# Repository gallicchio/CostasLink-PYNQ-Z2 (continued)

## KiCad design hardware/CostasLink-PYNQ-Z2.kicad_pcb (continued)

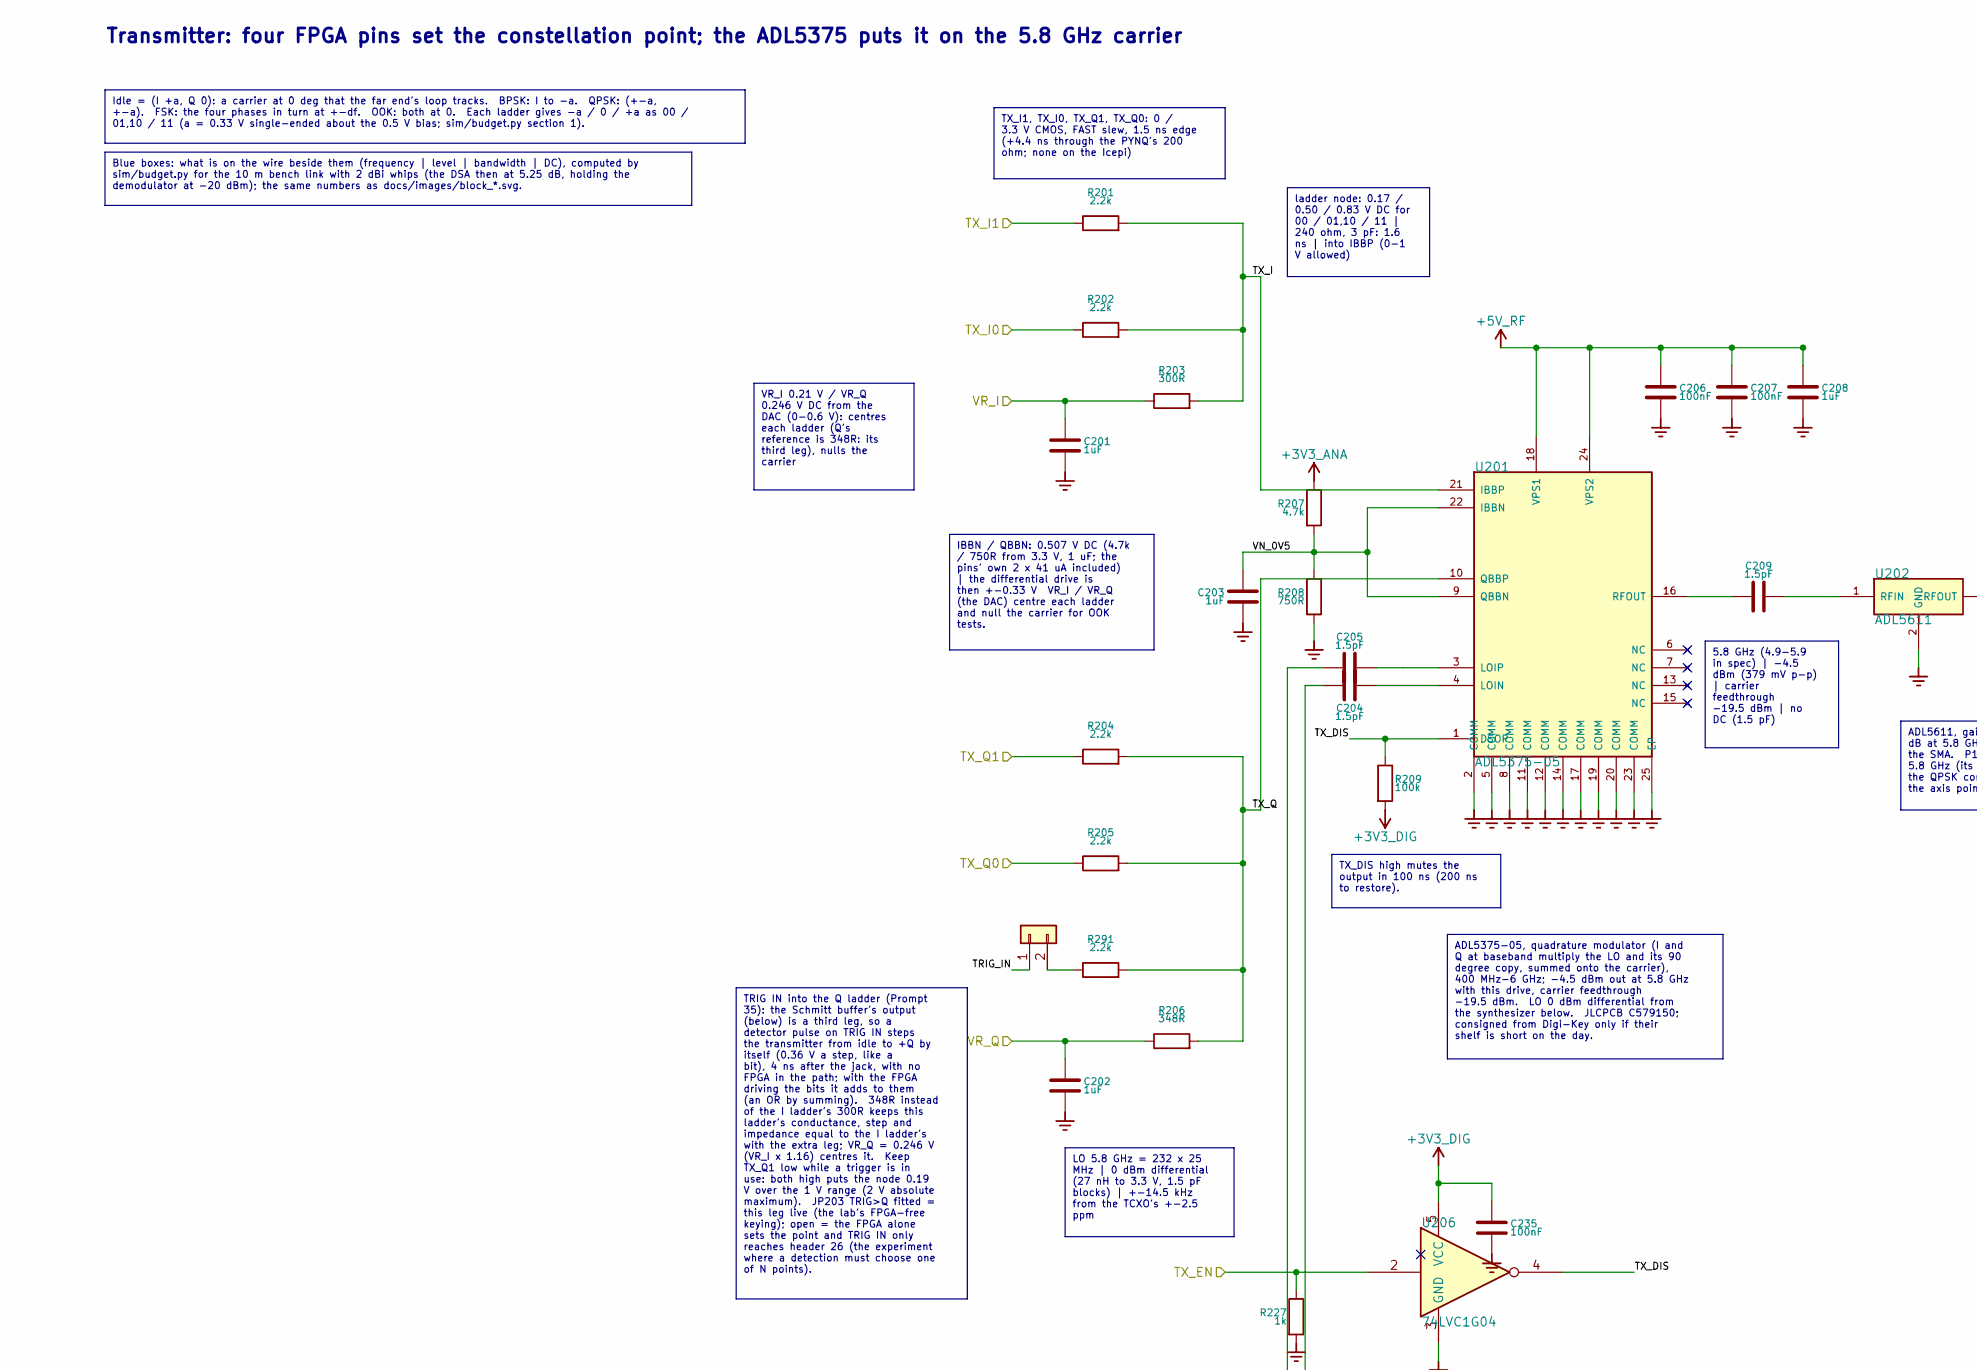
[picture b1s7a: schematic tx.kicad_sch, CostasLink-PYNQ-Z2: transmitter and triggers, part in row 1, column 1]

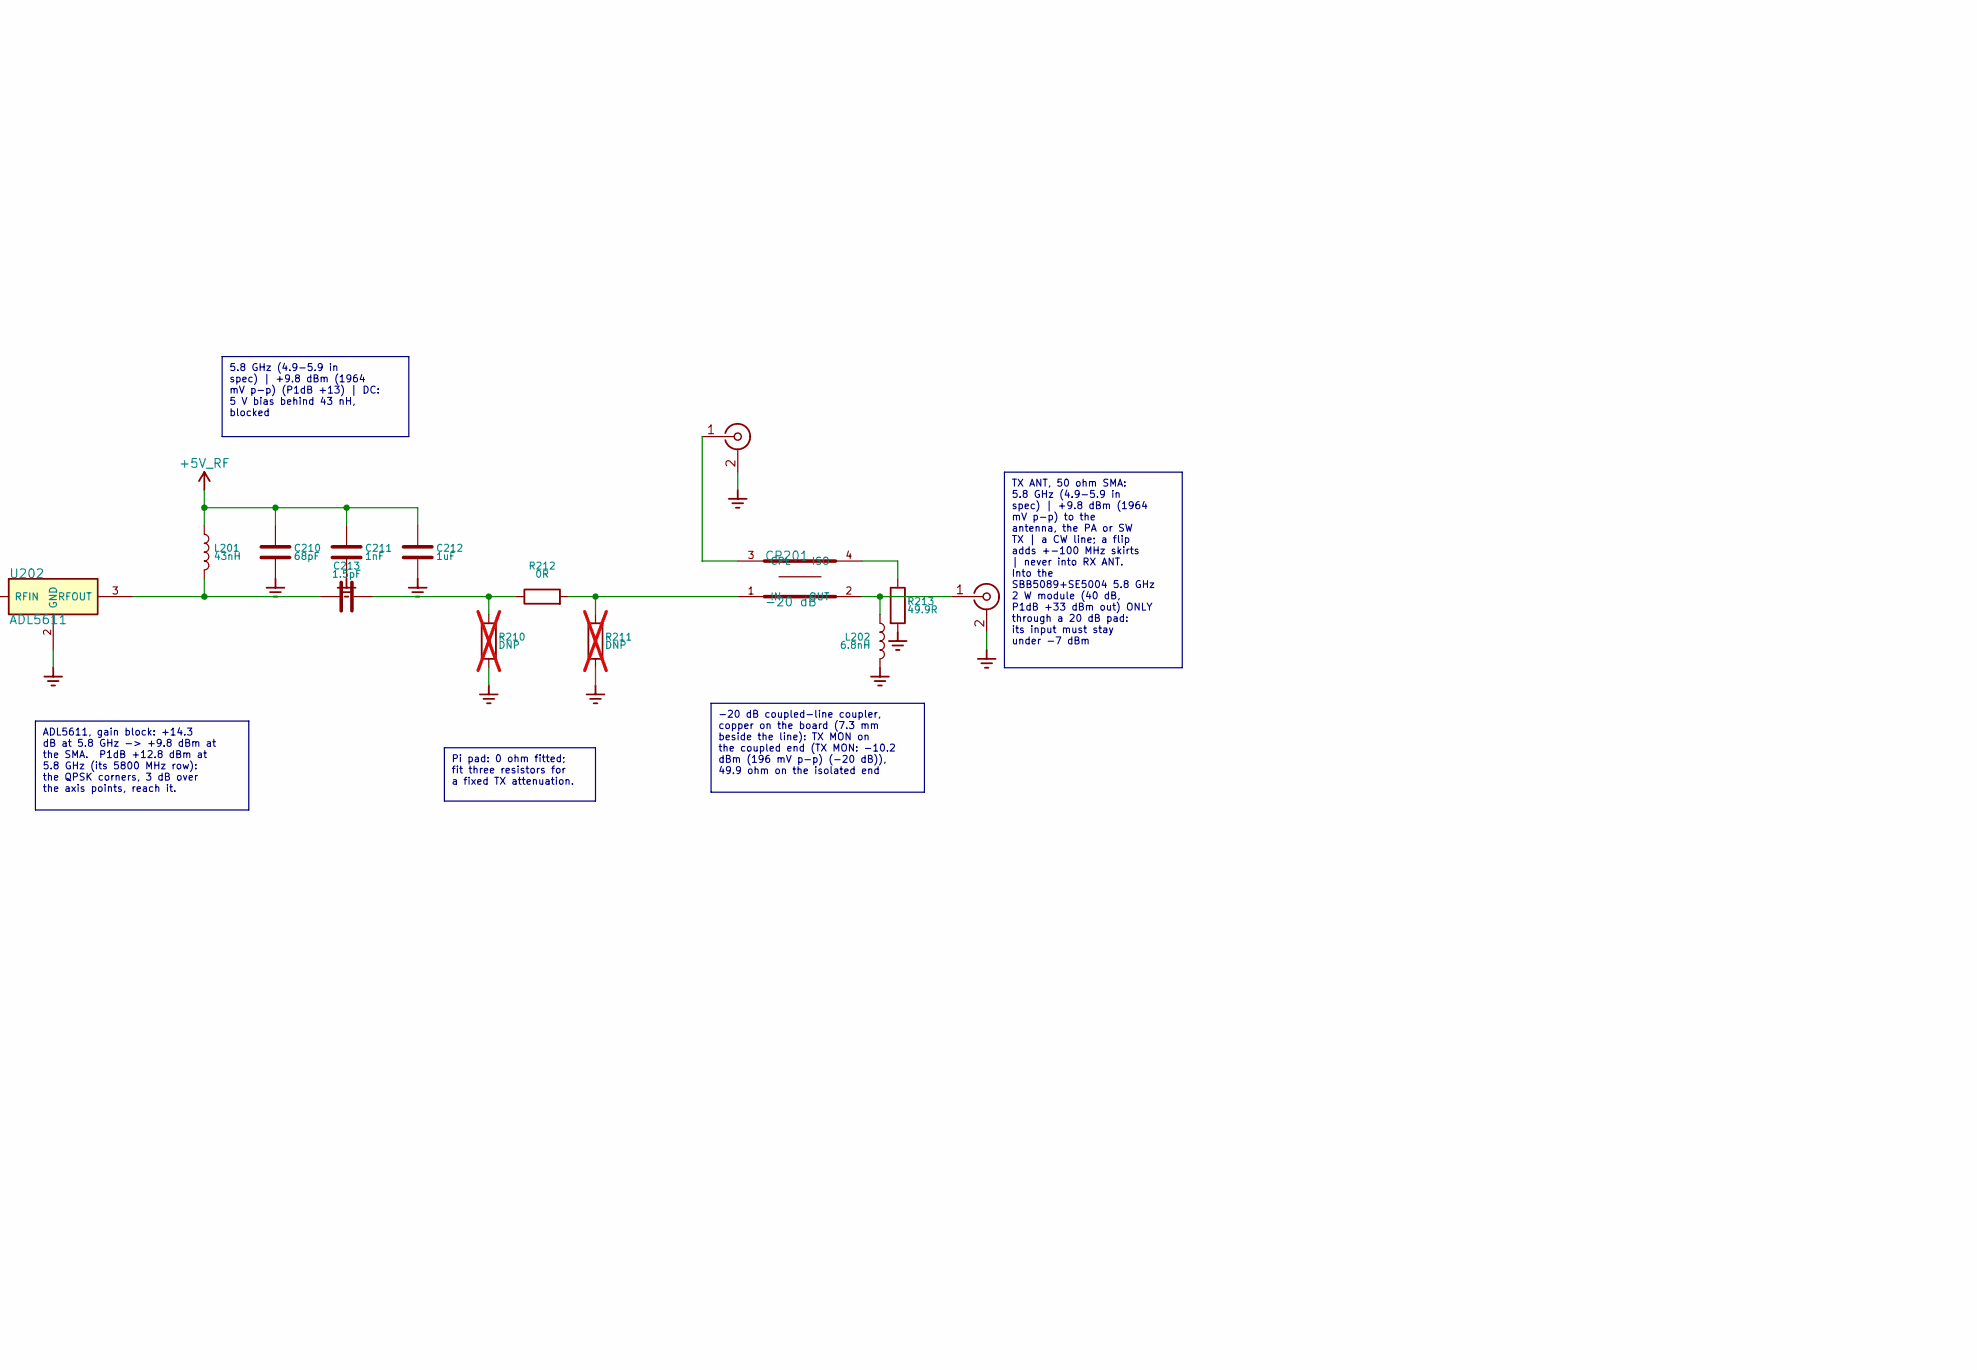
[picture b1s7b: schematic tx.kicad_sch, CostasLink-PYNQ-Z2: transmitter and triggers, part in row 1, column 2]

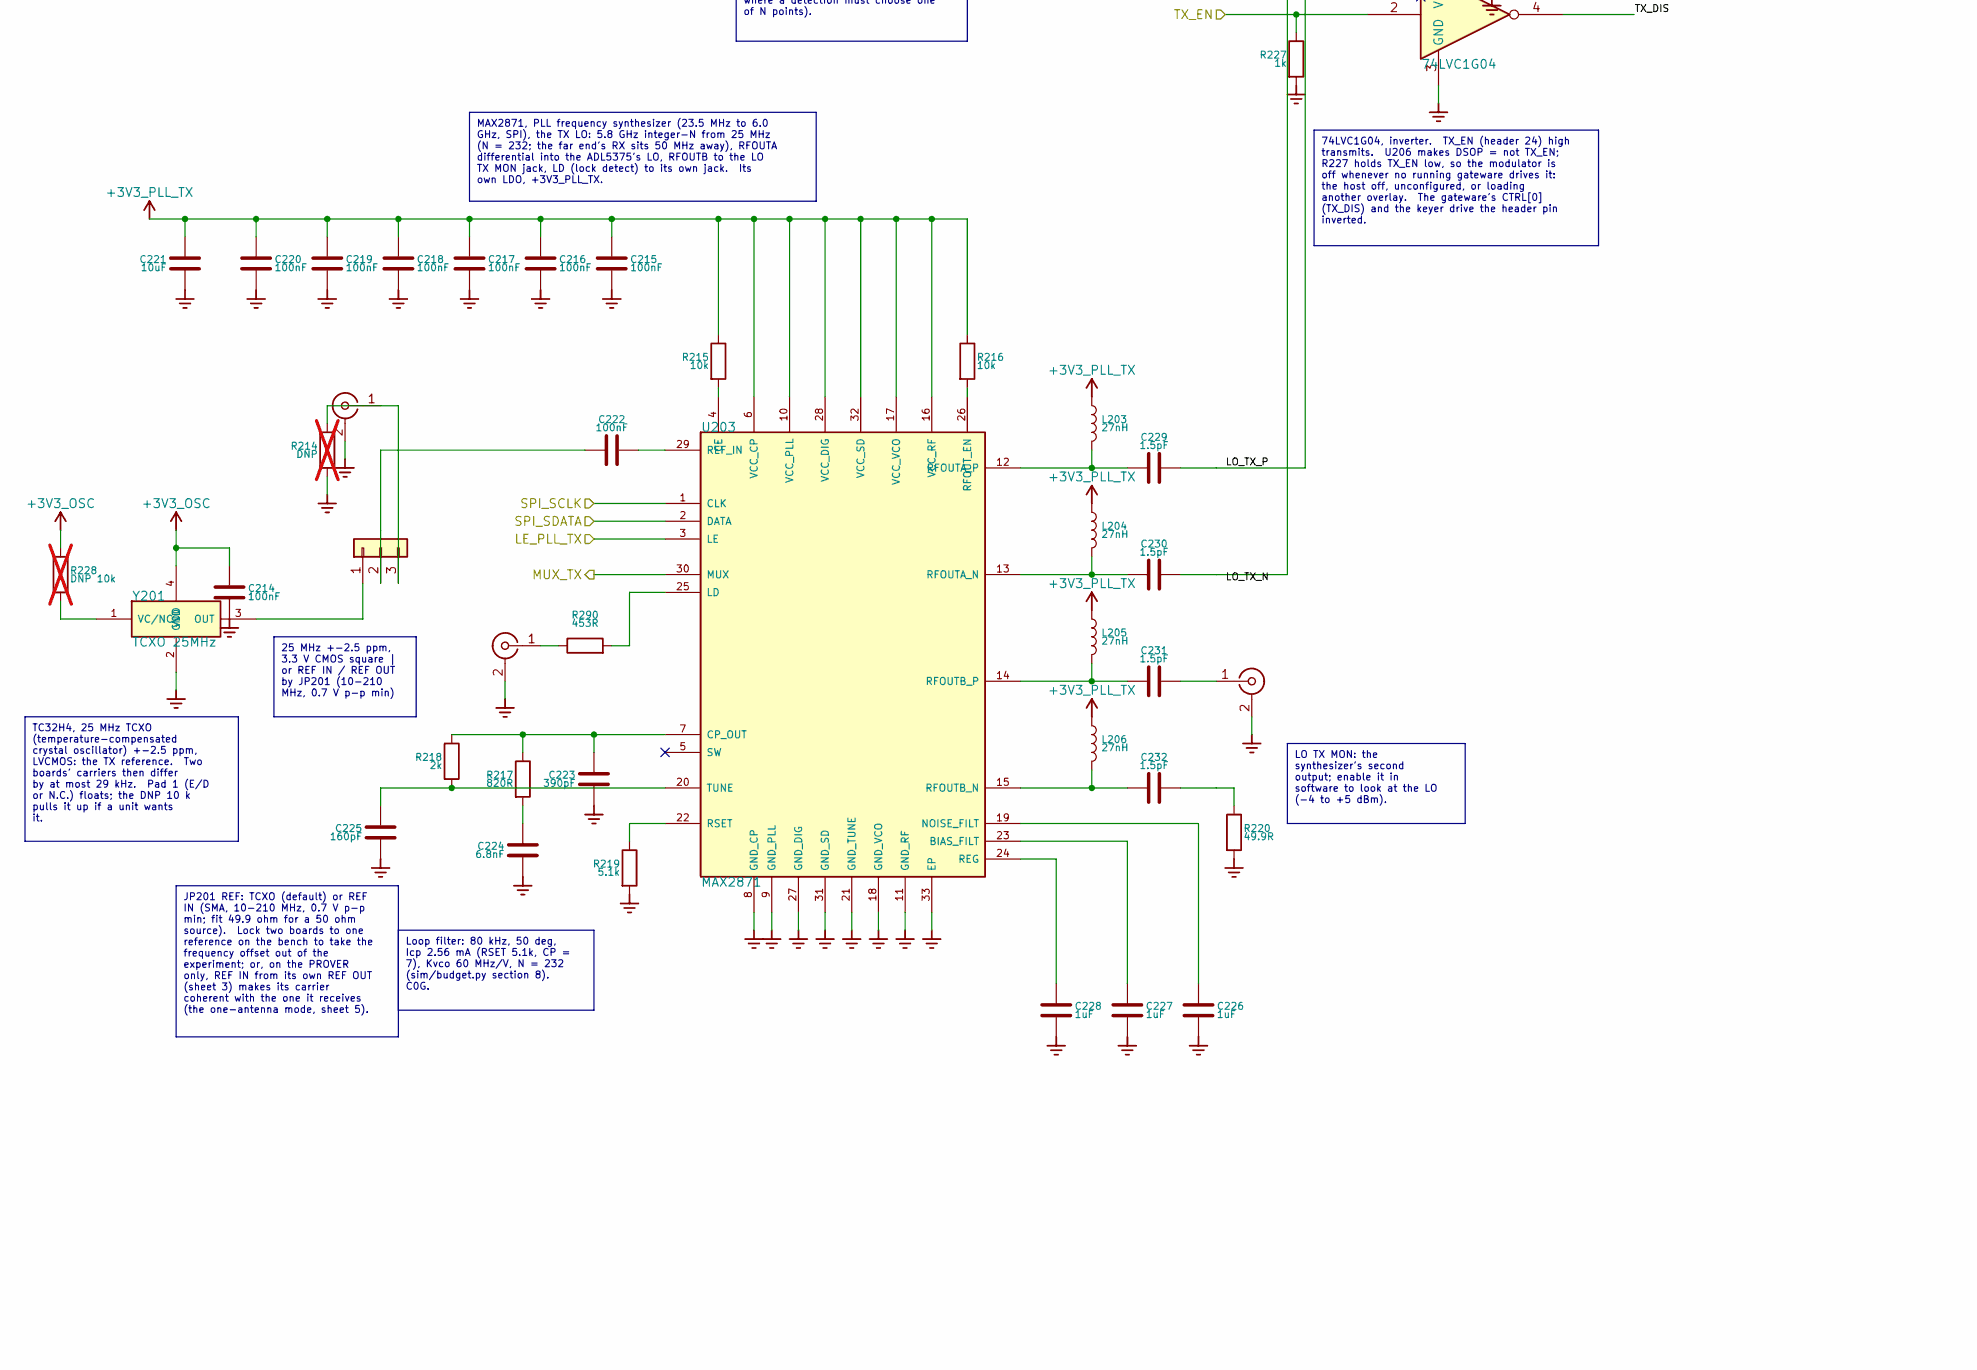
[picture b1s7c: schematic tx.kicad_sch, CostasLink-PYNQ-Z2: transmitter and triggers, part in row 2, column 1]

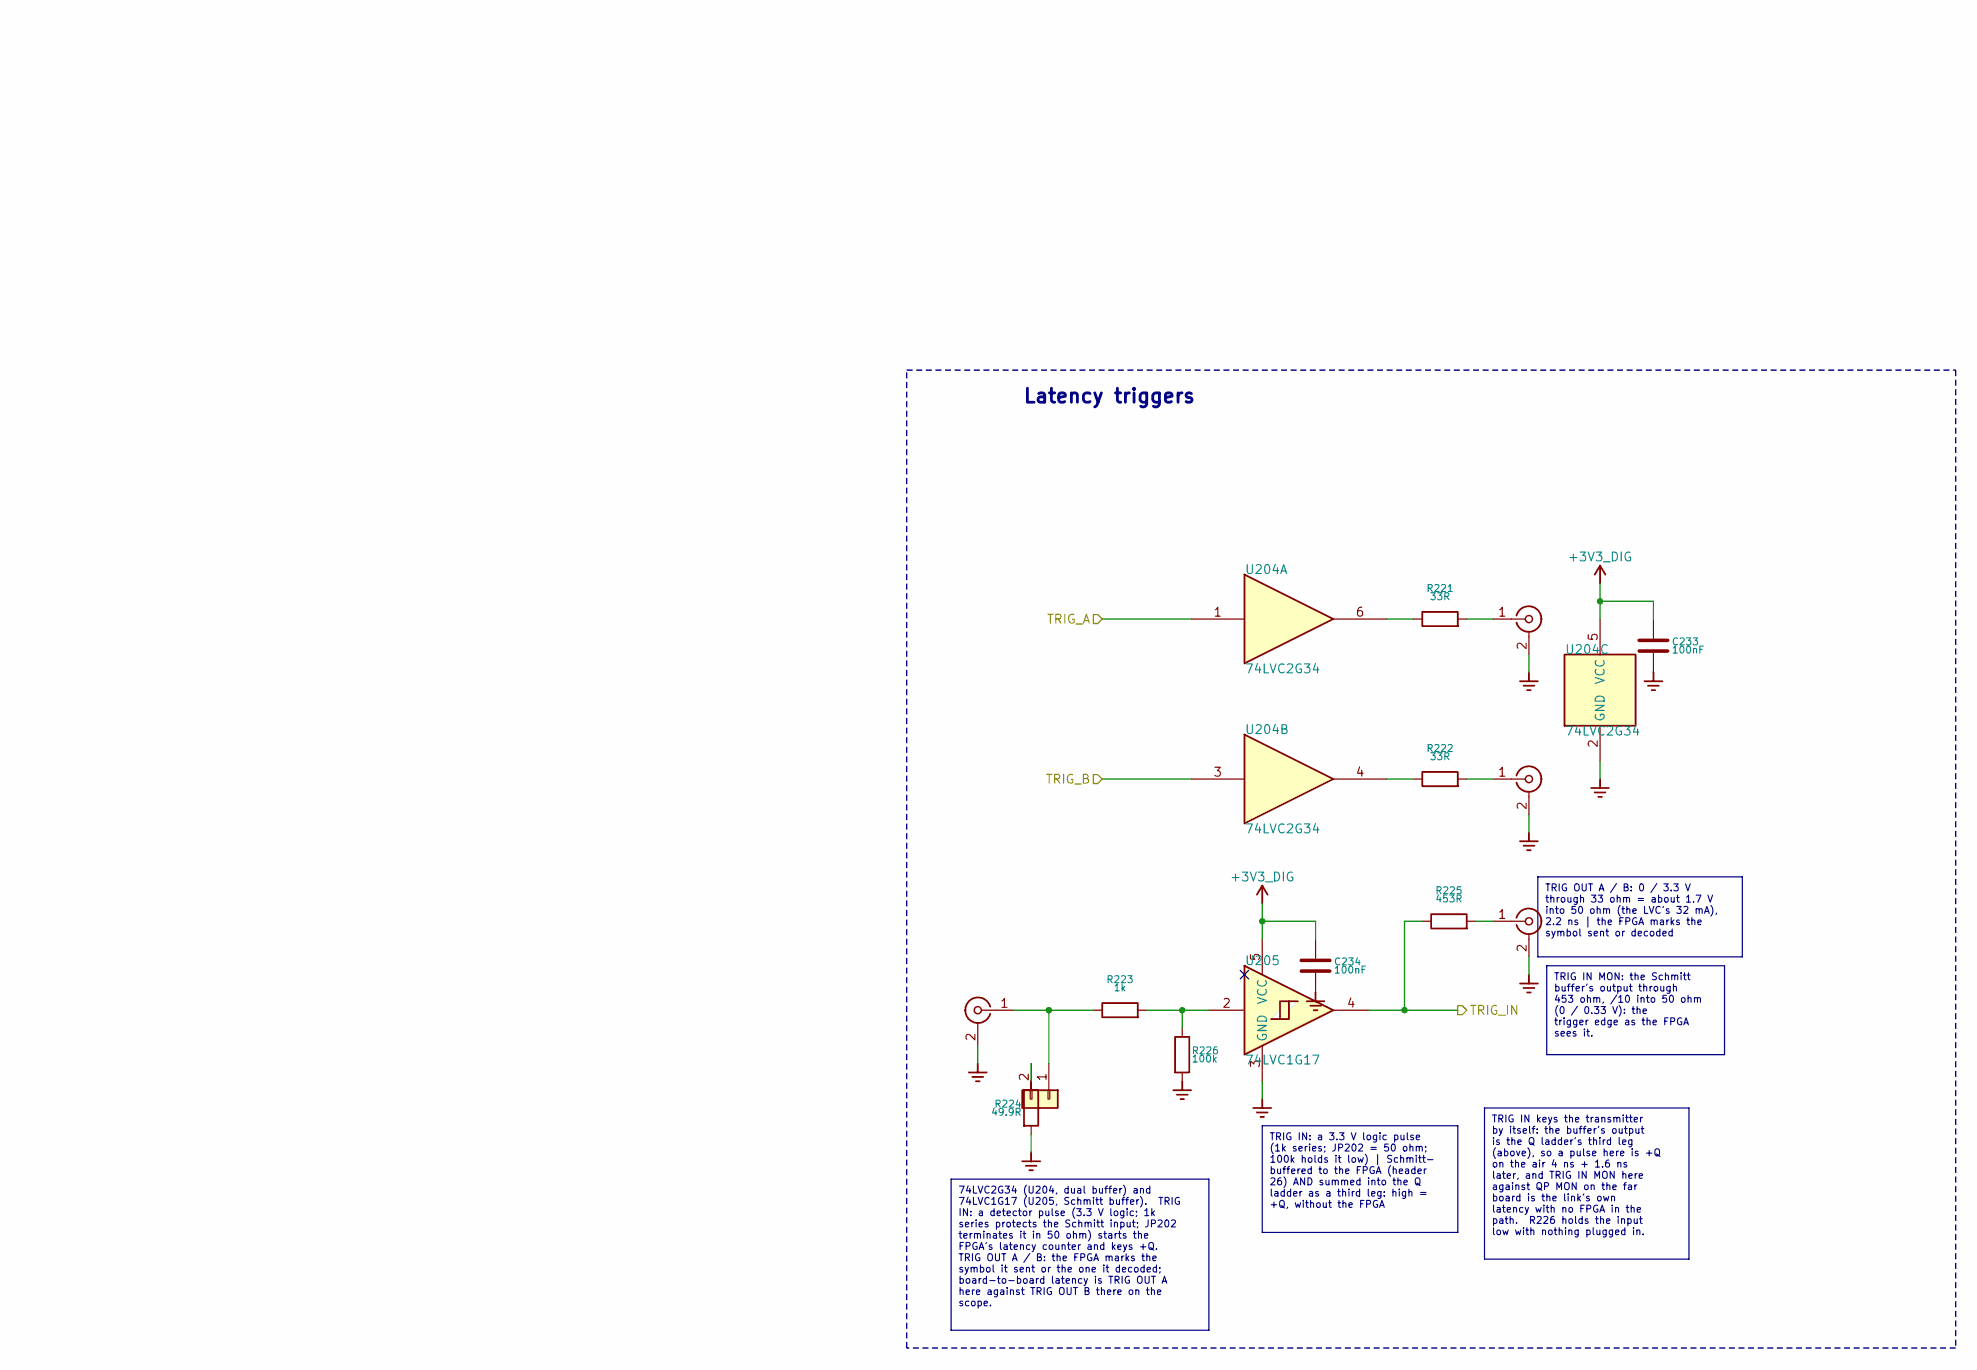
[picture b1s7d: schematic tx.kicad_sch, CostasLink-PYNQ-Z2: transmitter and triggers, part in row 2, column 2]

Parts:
C201, C202, C203, C208, C212, C226, C227, C228: 1uF; C_0402_1005Metric; MPN CL05A105KA5NQNC; LCSC C52923
C204, C205, C209, C213, C229, C230, C231, C232: 1.5pF; C_0402_1005Metric; MPN 0402CG1R5C500NT; LCSC C1552
C206, C207, C214, C215, C216, C217, C218, C219, C220, C222, C233, C234, C235: 100nF; C_0402_1005Metric; MPN CL05B104KO5NNNC; LCSC C1525
C210: 68pF; C_0402_1005Metric; MPN CL05C680JB5NNNC; LCSC C14441
C211: 1nF; C_0402_1005Metric; MPN 0402B102K500NT; LCSC C1523
C221: 10uF; C_0805_2012Metric; MPN CL21A106KAYNNNE; LCSC C15850
C223: 390pF; C_0402_1005Metric; MPN CC0402JRNPO9BN391; LCSC C282239
C224: 6.8nF; C_0603_1608Metric; MPN GRM1885C1H682JA01D; LCSC C162241
C225: 160pF; C_0402_1005Metric; MPN GCM1555C1H161JA16D; LCSC C2188753
CP201: -20 dB; Coupler_20dB_5.8GHz_CPWG
J201: TX MON; U.FL_Hirose_U.FL-R-SMT-1_Vertical; MPN U.FL-R-SMT-1(80); LCSC C88374
J202: TX ANT; SMA_BWSMA-KWE-Z001; MPN BWSMA-KWE-Z001; LCSC C496551
J203: REF IN; SMA_BWSMA-KWE-Z001; MPN BWSMA-KWE-Z001; LCSC C496551
J204: LO TX MON; U.FL_Hirose_U.FL-R-SMT-1_Vertical; MPN U.FL-R-SMT-1(80); LCSC C88374
J205: TRIG A; SMA_BWSMA-KWE-Z001; MPN BWSMA-KWE-Z001; LCSC C496551
J206: TRIG B; SMA_BWSMA-KWE-Z001; MPN BWSMA-KWE-Z001; LCSC C496551
J207: TRIG IN; SMA_BWSMA-KWE-Z001; MPN BWSMA-KWE-Z001; LCSC C496551
J208: TRIG IN MON; MMCX_BWMMCX-KE_Vertical; MPN BWMMCX-KE; LCSC C5137198
J290: LD TX; U.FL_Hirose_U.FL-R-SMT-1_Vertical; MPN U.FL-R-SMT-1(80); LCSC C88374
JP201: REF; PinHeader_1x03_P2.54mm_Vertical; MPN PZ254V-11-03P; LCSC C2937625
JP202: 50R; PinHeader_1x02_P2.54mm_Vertical; MPN PZ254V-11-02P; LCSC C492401
JP203: TRIG>Q; PinHeader_1x02_P2.54mm_Vertical; MPN PZ254V-11-02P; LCSC C492401
L201: 43nH; L_0603_1608Metric; MPN LQW18AN43NG00D; LCSC C113126
L202: 6.8nH; L_0402_1005Metric; MPN LQW15AN6N8G00D; LCSC C82919
L203, L204, L205, L206: 27nH; L_0402_1005Metric; MPN LQW15AN27NG80D; LCSC C882469
R201, R202, R204, R205, R291: 2.2k; R_0402_1005Metric; MPN 0402WGF2201TCE; LCSC C25879
R203: 300R; R_0402_1005Metric; MPN 0402WGF3000TCE; LCSC C25102
R206: 348R; R_0402_1005Metric; MPN 0402WGF3480TCE; LCSC C25107
R207: 4.7k; R_0402_1005Metric; MPN 0402WGF4701TCE; LCSC C25900
R208: 750R; R_0402_1005Metric; MPN 0402WGF7500TCE; LCSC C25132
R209, R226: 100k; R_0402_1005Metric; MPN 0402WGF1003TCE; LCSC C25741
R210, R211, R214: DNP; R_0402_1005Metric; MPN 0402WGF499JTCE; LCSC C25120; not fitted
R212: 0R; R_0402_1005Metric; MPN 0402WGF0000TCE; LCSC C17168
R213, R220, R224: 49.9R; R_0402_1005Metric; MPN 0402WGF499JTCE; LCSC C25120
R215, R216: 10k; R_0402_1005Metric; MPN 0402WGF1002TCE; LCSC C25744
R217: 820R; R_0402_1005Metric; MPN 0402WGF8200TCE; LCSC C25135
R218: 2k; R_0402_1005Metric; MPN 0402WGF2001TCE; LCSC C4109
R219: 5.1k; R_0402_1005Metric; MPN 0402WGF5101TCE; LCSC C25905
R221, R222: 33R; R_0402_1005Metric; MPN 0402WGF330JTCE; LCSC C25105
R223, R227: 1k; R_0402_1005Metric; MPN 0402WGF1001TCE; LCSC C11702
R225, R290: 453R; R_0402_1005Metric; MPN FRC0402F4530TS; LCSC C5126227
R228: DNP 10k; R_0402_1005Metric; MPN 0402WGF1002TCE; LCSC C25744; not fitted
U201: ADL5375-05; QFN-24-1EP_4x4mm_P0.5mm_EP2.6x2.6mm; MPN ADL5375-05ACPZ-R7; LCSC C579150
U202: ADL5611; SOT-89-3; MPN ADL5611ARKZ-R7; LCSC C208262
U203: MAX2871; QFN-32-1EP_5x5mm_P0.5mm_EP3.1x3.1mm; MPN MAX2871ETJ+T; LCSC C7458627
U204: 74LVC2G34; SOT-363_SC-70-6; MPN SN74LVC2G34DCKR; LCSC C14461
U205: 74LVC1G17; SOT-353_SC-70-5; MPN SN74LVC1G17DCKR; LCSC C10425
U206: 74LVC1G04; SOT-353_SC-70-5; MPN SN74LVC1G04DCKR; LCSC C8207
Y201: TCXO 25MHz; Crystal_SMD_3225-4Pin_3.2x2.5mm; MPN TC32H4-25.000-33GNDTNL; LCSC C5119013

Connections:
+3V3_ANA: R207.1; also elsewhere on the board
+3V3_DIG: C233.1, C234.1, C235.1, R209.2, U204.5 (VCC), U205.5 (VCC), U206.5 (VCC); also elsewhere on the board
+3V3_OSC: C214.1, R228.1, Y201.4 (VDD); also elsewhere on the board
+3V3_PLL_TX: C215.1, C216.1, C217.1, C218.1, C219.1, C220.1, C221.1, L203.1, L204.1, L205.1, L206.1, R215.1, R216.1, U203.6 (VCC_CP), U203.10 (VCC_PLL), U203.16 (VCC_RF), U203.17 (VCC_VCO), U203.28 (VCC_DIG), U203.32 (VCC_SD); also elsewhere on the board
+5V_RF: C206.1, C207.1, C208.1, C210.1, C211.1, C212.1, L201.1, U201.18 (VPS1), U201.24 (VPS2); also elsewhere on the board
/Power and FPGA header/LE_PLL_TX: U203.3 (LE); also elsewhere on the board
/Power and FPGA header/MUX_TX: U203.30 (MUX); also elsewhere on the board
/Power and FPGA header/SPI_SCLK: U203.1 (CLK); also elsewhere on the board
/Power and FPGA header/SPI_SDATA: U203.2 (DATA); also elsewhere on the board
/Power and FPGA header/TRIG_A: U204.1; also elsewhere on the board
/Power and FPGA header/TRIG_B: U204.3; also elsewhere on the board
/Power and FPGA header/TX_EN: R227.1, U206.2; also elsewhere on the board
/Power and FPGA header/TX_I0: R202.1; also elsewhere on the board
/Power and FPGA header/TX_I1: R201.1; also elsewhere on the board
/Power and FPGA header/TX_Q0: R205.1; also elsewhere on the board
/Receiver and Costas loop/VR_I: C201.1, R203.1; also elsewhere on the board
/Receiver and Costas loop/VR_Q: C202.1, R206.1; also elsewhere on the board
/Transmitter and triggers/LO_TX_N: C205.1, C230.2
/Transmitter and triggers/LO_TX_P: C204.1, C229.2
/Transmitter and triggers/TX_DIS: R209.1, U201.1 (DSOP), U206.4
/Transmitter and triggers/TX_I: R201.2, R202.2, R203.2, U201.21 (IBBP)
/Transmitter and triggers/TX_Q: R204.2, R205.2, R206.2, R291.2, U201.10 (QBBP)
/Transmitter and triggers/VN_0V5: C203.1, R207.2, R208.1, U201.9 (QBBN), U201.22 (IBBN)
unnamed: C213.2, R210.1, R212.1
unnamed: C224.1, R217.2
unnamed: C232.2, R220.1
unnamed: CP201.3 (CPL), J201.1 (In)
unnamed: CP201.1 (IN), R211.1, R212.2
unnamed: CP201.4 (ISO), R213.1
unnamed: CP201.2 (OUT), J202.1 (In), L202.1
unnamed: J203.1 (In), JP201.3, R214.1
unnamed: C231.2, J204.1 (In)
unnamed: J205.1 (In), R221.2
unnamed: J206.1 (In), R222.2
unnamed: J207.1 (In), JP202.1, R223.1
unnamed: J208.1 (In), R225.2
unnamed: J290.1 (In), R290.1
unnamed: JP201.1, Y201.3 (OUT)
unnamed: C222.1, JP201.2
unnamed: JP202.2, R224.1
unnamed: JP203.2, R291.1
unnamed: R221.1, U204.6
unnamed: R222.1, U204.4
unnamed: C204.2, U201.4 (LOIN)
unnamed: C205.2, U201.3 (LOIP)
unnamed: C209.1, U201.16 (RFOUT)
unnamed: C209.2, U202.1 (RFIN)
unnamed: C213.1, L201.2, U202.3 (RFOUT)
unnamed: C227.1, U203.23 (BIAS_FILT)
unnamed: R215.2, U203.4 (CE)
unnamed: C223.1, R217.1, R218.1, U203.7 (CP_OUT)
unnamed 207: R290.2, U203.25 (LD); also elsewhere on the board
unnamed: C226.1, U203.19 (NOISE_FILT)
unnamed: C222.2, U203.29 (REF_IN)
unnamed: C228.1, U203.24 (REG)
unnamed: C230.1, L204.2, U203.13 (RFOUTA_N)
unnamed: C229.1, L203.2, U203.12 (RFOUTA_P)
unnamed: C232.1, L206.2, U203.15 (RFOUTB_N)
unnamed: C231.1, L205.2, U203.14 (RFOUTB_P)
unnamed: R216.2, U203.26 (RFOUT_EN)
unnamed: R219.1, U203.22 (RSET)
unnamed: C225.1, R218.2, U203.20 (TUNE)
unnamed: R228.2, Y201.1 (VC/NC)

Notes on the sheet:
Transmitter: four FPGA pins set the constellation point; the ADL5375 puts it on the 5.8 GHz carrier
Latency triggers
Idle = (I +a, Q 0): a carrier at 0 deg that the far end's loop tracks. BPSK: I to -a. QPSK: (+-a, +-a). FSK: the four phases in turn at +-df. OOK: both at 0. Each ladder gives -a / 0 / +a as 00 / 01,10 / 11 (a = 0.33 V single-ended about the 0.5 V bias; sim/budget.py section 1).
Blue boxes: what is on the wire beside them (frequency | level | bandwidth | DC), computed by sim/budget.py for the 10 m bench link with 2 dBi whips (the DSA then at 5.25 dB, holding the demodulator at -20 dBm); the same numbers as docs/images/block_*.svg.
TX_I1, TX_I0, TX_Q1, TX_Q0: 0 / 3.3 V CMOS, FAST slew, 1.5 ns edge (+4.4 ns through the PYNQ's 200 ohm; none on the Icepi)
ladder node: 0.17 / 0.50 / 0.83 V DC for 00 / 01,10 / 11 | 240 ohm, 3 pF: 1.6 ns | into IBBP (0-1 V allowed)
VR_I 0.21 V / VR_Q 0.246 V DC from the DAC (0-0.6 V): centres each ladder (Q's reference is 348R: its third leg), nulls the carrier
TRIG IN into the Q ladder (Prompt 35): the Schmitt buffer's output (below) is a third leg, so a detector pulse on TRIG IN steps the transmitter from idle to +Q by itself (0.36 V a step, like a bit), 4 ns after the jack, with no FPGA in the path; with the FPGA driving the bits it adds to them (an OR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
IBBN / QBBN: 0.507 V DC (4.7k / 750R from 3.3 V, 1 uF; the pins' own 2 x 41 uA included) | the differential drive is then +-0.33 V VR_I / VR_Q (the DAC) centre each ladder and null the carrier for OOK tests.
TX_DIS high mutes the output in 100 ns (200 ns to restore).
74LVC1G04, inverter. TX_EN (header 24) high transmits. U206 makes DSOP = not TX_EN; R227 holds TX_EN low, so the modulator is off whenever no running gateware drives it: the host off, unconfigured, or loading another overlay. The gateware's CTRL[0] (TX_DIS) and the keyer drive the header pin invert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
ADL5375-05, quadrature modulator (I and Q at baseband multiply the LO and its 90 degree copy, summed onto the carrier), 400 MHz-6 GHz; -4.5 dBm out at 5.8 GHz with this drive, carrier feedthrough -19.5 dBm. LO 0 dBm differential from the synthesizer below. JLCPCB C579150; consigned from Digi-Key on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
5.8 GHz (4.9-5.9 in spec) | -4.5 dBm (379 mV p-p) | carrier feedthrough -19.5 dBm | no DC (1.5 pF)
ADL5611, gain block: +14.3 dB at 5.8 GHz -> +9.8 dBm at the SMA. P1dB +12.8 dBm at 5.8 GHz (its 5800 MHz row): the QPSK corners, 3 dB over the axis points, reach it.
5.8 GHz (4.9-5.9 in spec) | +9.8 dBm (1964 mV p-p) (P1dB +13) | DC: 5 V bias behind 43 nH, blocked
Pi pad: 0 ohm fitted; fit three resistors for a fixed TX attenuation.
-20 dB coupled-line coupler, copper on the board (7.3 mm beside the line): TX MON on the coupled end (TX MON: -10.2 dBm (196 mV p-p) (-20 dB)), 49.9 ohm on the isolated end
TX ANT, 50 ohm SMA: 5.8 GHz (4.9-5.9 in spec) | +9.8 dBm (1964 mV p-p) to the antenna, the PA or SW TX | a CW line; a flip adds +-100 MHz skirts | never into RX ANT. Into the SBB5089+SE5004 5.8 GHz 2 W module (40 dB, P1dB +33 dBm out) ONLY through a 20 dB pad: its input must stay under -7 dBm
TC32H4, 25 MHz TCXO (temperature-compensated crystal oscillator) +-2.5 ppm, LVCMOS: the TX reference. Two boards' carriers then differ by at most 29 kHz. Pad 1 (E/D or N.C.) floats; the DNP 10 k pulls it up if a unit wants it.
25 MHz +-2.5 ppm, 3.3 V CMOS square | or REF IN / REF OUT by JP201 (10-210 MHz, 0.7 V p-p min)
JP201 REF: TCXO (default) or REF IN (SMA, 10-210 MHz, 0.7 V p-p min; fit 49.9 ohm for a 50 ohm source). Lock two boards to one reference on the bench to take the frequency offset out of the experiment; or, on the PROVER only, REF IN from its own REF OUT (sheet 3) makes its carrier coherent with the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
Loop filter: 80 kHz, 50 deg, Icp 2.56 mA (RSET 5.1k, CP = 7), Kvco 60 MHz/V, N = 232 (sim/budget.py section 8). C0G.
LO TX MON: the synthesizer's second output; enable it in software to look at the LO (-4 to +5 dBm).
LO 5.8 GHz = 232 x 25 MHz | 0 dBm differential (27 nH to 3.3 V, 1.5 pF blocks) | +-14.5 kHz from the TCXO's +-2.5 ppm
MAX2871, PLL frequency synthesizer (23.5 MHz to 6.0 GHz, SPI), the TX LO: 5.8 GHz integer-N from 25 MHz (N = 232; the far end's RX sits 50 MHz away), RFOUTA differential into the ADL5375's LO, RFOUTB to the LO TX MON jack, LD (lock detect) to its own jack. Its own LDO, +3V3_PLL_TX.
TRIG OUT A / B: 0 / 3.3 V through 33 ohm = about 1.7 V into 50 ohm (the LVC's 32 mA), 2.2 ns | the FPGA marks the symbol sent or decoded
TRIG IN MON: the Schmitt buffer's output through 453 ohm, /10 into 50 ohm (0 / 0.33 V): the trigger edge as the FPGA sees it.
TRIG IN keys the transmitter by itself: the buffer's output is the Q ladder's third leg (above), so a pulse here is +Q on the air 4 ns + 1.6 ns later, and TRIG IN MON here against QP MON on the far board is the link's own latency with no FPGA in the path. R226 holds the input low with nothing plugg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
TRIG IN: a 3.3 V logic pulse (1k series; JP202 = 50 ohm; 100k holds it low) | Schmitt- buffered to the FPGA (header 26) AND summed into the Q ladder as a third leg: high = +Q, without the FPGA
74LVC2G34 (U204, dual buffer) and 74LVC1G17 (U205, Schmitt buffer). TRIG IN: a detector pulse (3.3 V logic; 1k series protects the Schmitt input; JP202 terminates it in 50 ohm) starts the FPGA's latency counter and keys +Q. TRIG OUT A / B: the FPGA marks the symbol it sent or the one it decoded; bo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

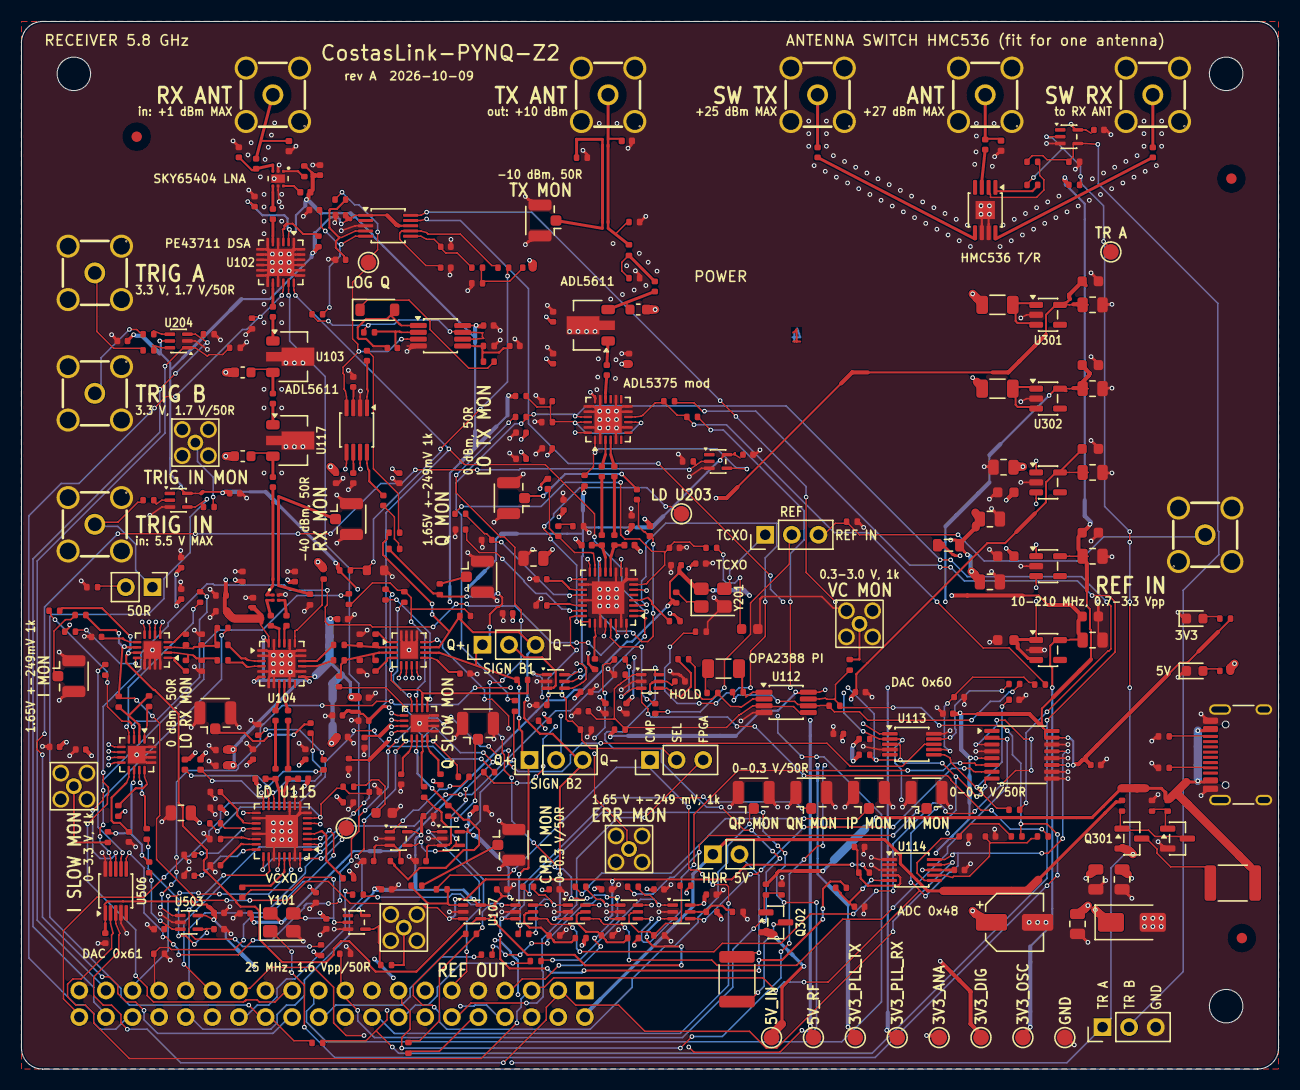
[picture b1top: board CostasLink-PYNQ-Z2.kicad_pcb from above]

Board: 4 copper layers, 120.0 x 100.0 mm, 422 parts (1 on the bottom side), 257 nets.

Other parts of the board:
TP201: LD U203; TestPoint_Pad_D1.5mm
TP401: TR A; TestPoint_Pad_D1.5mm

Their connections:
/Antenna switch: one antenna by T/R/TR_A: TP401.1; also elsewhere on the board
unnamed 207: TP201.1; also elsewhere on the board

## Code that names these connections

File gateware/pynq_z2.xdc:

# CostasLink-PYNQ-Z2 on the PYNQ-Z2's Raspberry Pi header.  Made by gateware/gen_xdc.py from gen/pins.py.
# Header pin -> Zynq package pin from the GPSDO-PYNQ-Z2 board's verified table (TUL schematic sheet 4).
# Clock-capable header pins on this board: [10, 11, 13, 18, 26, 31, 35, 40] (18 and 26 are also clock-capable on the Icepi Zero).

# header  3  IO_L22P_T3_34              I2C to the DAC and ADC; 2k2 pull-up on the PYNQ
set_property PACKAGE_PIN W18 [get_ports {i2c_sda}]
set_property IOSTANDARD LVCMOS33 [get_ports {i2c_sda}]
set_property PULLUP true [get_ports {i2c_sda}]

# header  5  IO_L22N_T3_34              I2C clock; 2k2 pull-up on the PYNQ
set_property PACKAGE_PIN W19 [get_ports {i2c_scl}]
set_property IOSTANDARD LVCMOS33 [get_ports {i2c_scl}]
set_property PULLUP true [get_ports {i2c_scl}]

# header  7  IO_L17P_T2_34              TX I ladder, bit 1
set_property PACKAGE_PIN Y18 [get_ports {tx_i1}]
set_property IOSTANDARD LVCMOS33 [get_ports {tx_i1}]
set_property DRIVE 8 [get_ports {tx_i1}]
set_property SLEW FAST [get_ports {tx_i1}]

# header  8  IO_L22P_T3_13              comparator: Q < -Vth
set_property PACKAGE_PIN V6 [get_ports {cmp_qn}]
set_property IOSTANDARD LVCMOS33 [get_ports {cmp_qn}]

# header 10  IO_L13N_T2_MRCC_13         comparator: Q > +Vth (MRCC N of the pair with pin 18)
set_property PACKAGE_PIN Y6 [get_ports {cmp_qp}]
set_property IOSTANDARD LVCMOS33 [get_ports {cmp_qp}]

# header 11  IO_L11P_T1_SRCC_13         TX I ladder, bit 0
set_property PACKAGE_PIN U7 [get_ports {tx_i0}]
set_property IOSTANDARD LVCMOS33 [get_ports {tx_i0}]
set_property DRIVE 8 [get_ports {tx_i0}]
set_property SLEW FAST [get_ports {tx_i0}]

# header 12  IO_L1P_T0_AD0P_35          the Costas switch's select when JP1 is set to FPGA
set_property PACKAGE_PIN C20 [get_ports {loop_sel}]
set_property IOSTANDARD LVCMOS33 [get_ports {loop_sel}]
set_property DRIVE 4 [get_ports {loop_sel}]
set_property SLEW SLOW [get_ports {loop_sel}]

# header 13  IO_L11N_T1_SRCC_13         TX Q ladder, bit 1 (rpio_27: absent from the stock XDC)
set_property PACKAGE_PIN V7 [get_ports {tx_q1}]
set_property IOSTANDARD LVCMOS33 [get_ports {tx_q1}]
set_property DRIVE 8 [get_ports {tx_q1}]
set_property SLEW FAST [get_ports {tx_q1}]

# header 15  IO_L17N_T2_13              TX Q ladder, bit 0
set_property PACKAGE_PIN U8 [get_ports {tx_q0}]
set_property IOSTANDARD LVCMOS33 [get_ports {tx_q0}]
set_property DRIVE 8 [get_ports {tx_q0}]
set_property SLEW FAST [get_ports {tx_q0}]

# header 16  IO_L22N_T3_13              I window, - side: I_N above V_TIN (fast; the PYNQ's 2k2 pull-up here is a harmless load)
set_property PACKAGE_PIN W6 [get_ports {cmp_in}]
set_property IOSTANDARD LVCMOS33 [get_ports {cmp_in}]

# header 18  IO_L13P_T2_MRCC_13         comparator: sign(I) = the data (clock-capable on both boards)
set_property PACKAGE_PIN Y7 [get_ports {cmp_i}]
set_property IOSTANDARD LVCMOS33 [get_ports {cmp_i}]

# header 19  IO_L15P_T2_DQS_13          high opens the Costas integrator's input (VC frozen)
set_property PACKAGE_PIN V8 [get_ports {loop_hold}]
set_property IOSTANDARD LVCMOS33 [get_ports {loop_hold}]
set_property DRIVE 4 [get_ports {loop_hold}]
set_property SLEW SLOW [get_ports {loop_hold}]

# header 21  IO_L21N_T3_DQS_13          MAX2871 (TX) latch enable
set_property PACKAGE_PIN V10 [get_ports {le_pll_tx}]
set_property IOSTANDARD LVCMOS33 [get_ports {le_pll_tx}]
set_property DRIVE 4 [get_ports {le_pll_tx}]
set_property SLEW SLOW [get_ports {le_pll_tx}]

# header 22  IO_L15N_T2_DQS_AD12N_35    I window, + side: I_P above V_TIP (fast; sheet 7, Response 14)
set_property PACKAGE_PIN F20 [get_ports {cmp_ip}]
set_property IOSTANDARD LVCMOS33 [get_ports {cmp_ip}]

# header 23  IO_L16P_T2_13              MAX2871 (TX) MUX: lock detect or register readback
set_property PACKAGE_PIN W10 [get_ports {mux_tx}]
set_property IOSTANDARD LVCMOS33 [get_ports {mux_tx}]

# header 24  IO_L15P_T2_DQS_AD12P_35    TX enable, high = transmit: U206 inverts it onto the ADL5375's DSOP; 1 k to ground here, so a host that is off, unconfigured or not driving it leaves the modulator off
set_property PACKAGE_PIN F19 [get_ports {tx_en}]
set_property IOSTANDARD LVCMOS33 [get_ports {tx_en}]
set_property DRIVE 4 [get_ports {tx_en}]
set_property SLEW SLOW [get_ports {tx_en}]

# header 26  IO_L12N_T1_MRCC_34         external trigger (a detector pulse) through the Schmitt buffer (clock-capable on both)
set_property PACKAGE_PIN U19 [get_ports {trig_in}]
set_property IOSTANDARD LVCMOS33 [get_ports {trig_in}]

# header 27  IO_L7P_T1_34               antenna switch control A; B = not A is made on the board (also on J303; 2k2 pull-up on the PYNQ)
set_property PACKAGE_PIN Y16 [get_ports {tr_a}]
set_property IOSTANDARD LVCMOS33 [get_ports {tr_a}]
set_property DRIVE 8 [get_ports {tr_a}]
set_property SLEW FAST [get_ports {tr_a}]

# header 28  IO_L7N_T1_34               slow path: Q < -Vth2
set_property PACKAGE_PIN Y17 [get_ports {cmp_qn_s}]
set_property IOSTANDARD LVCMOS33 [get_ports {cmp_qn_s}]

# header 29  IO_L17N_T2_34              SPI data to the MAX2871s and the PE43711
set_property PACKAGE_PIN Y19 [get_ports {spi_sdata}]
set_property IOSTANDARD LVCMOS33 [get_ports {spi_sdata}]
set_property DRIVE 4 [get_ports {spi_sdata}]
set_property SLEW SLOW [get_ports {spi_sdata}]

# header 31  IO_L12P_T1_MRCC_34         SPI clock: both MAX2871s and the PE43711
set_property PACKAGE_PIN U18 [get_ports {spi_sclk}]
set_property IOSTANDARD LVCMOS33 [get_ports {spi_sclk}]
set_property DRIVE 4 [get_ports {spi_sclk}]
set_property SLEW SLOW [get_ports {spi_sclk}]

# header 32  IO_L1N_T0_AD0N_35          slow path: Q > +Vth2
set_property PACKAGE_PIN B20 [get_ports {cmp_qp_s}]
set_property IOSTANDARD LVCMOS33 [get_ports {cmp_qp_s}]

# header 33  IO_L15N_T2_DQS_13          MAX2871 (RX) latch enable
set_property PACKAGE_PIN W8 [get_ports {le_pll_rx}]
set_property IOSTANDARD LVCMOS33 [get_ports {le_pll_rx}]
set_property DRIVE 4 [get_ports {le_pll_rx}]
set_property SLEW SLOW [get_ports {le_pll_rx}]

# header 35  IO_L14N_T2_SRCC_13         MAX2871 (RX) MUX (Icepi bank 0: no GDDRX2)
set_property PACKAGE_PIN Y8 [get_ports {mux_rx}]
set_property IOSTANDARD LVCMOS33 [get_ports {mux_rx}]

# header 36  IO_L2P_T0_AD8P_35          PE43711 latch enable
set_property PACKAGE_PIN B19 [get_ports {le_dsa}]
set_property IOSTANDARD LVCMOS33 [get_ports {le_dsa}]
set_property DRIVE 4 [get_ports {le_dsa}]
set_property SLEW SLOW [get_ports {le_dsa}]

# header 37  IO_L16N_T2_13              trigger out A (buffered to its SMA) (Icepi bank 0: no GDDRX2)
set_property PACKAGE_PIN W9 [get_ports {trig_a}]
set_property IOSTANDARD LVCMOS33 [get_ports {trig_a}]
set_property DRIVE 8 [get_ports {trig_a}]
set_property SLEW FAST [get_ports {trig_a}]

# header 38  IO_L2N_T0_AD8N_35          trigger out B (buffered to its SMA)
set_property PACKAGE_PIN A20 [get_ports {trig_b}]
set_property IOSTANDARD LVCMOS33 [get_ports {trig_b}]
set_property DRIVE 8 [get_ports {trig_b}]
set_property SLEW FAST [get_ports {trig_b}]

# header 40  IO_L14P_T2_SRCC_13         slow path: sign(I) through the 5 MHz stage (confirms or vetoes CMP_I)
set_property PACKAGE_PIN Y9 [get_ports {cmp_i_s}]
set_property IOSTANDARD LVCMOS33 [get_ports {cmp_i_s}]

# the PYNQ-Z2's 125 MHz clock (Ethernet PHY), as the stock constraints have it
set_property PACKAGE_PIN H16 [get_ports {sysclk}]
set_property IOSTANDARD LVCMOS33 [get_ports {sysclk}]
create_clock -period 8.000 -name sysclk [get_ports {sysclk}]

# the command UART of the first firmware (gateware/uart_cmd.v).  The PYNQ-Z2's own USB UART belongs to the PS
# (MIO), not the PL, so a USB-UART dongle goes on the Arduino header's D0 (RX) / D1 (TX): T14 / U12 = ar[0] / ar[1]
# in TUL's PYNQ-Z2 master XDC (from memory, not a measured table: verify against the schematic before building).
# The register file moves to AXI-Lite on the PYNQ later (README.md), and these two lines go.
set_property PACKAGE_PIN T14 [get_ports {uart_rx}]
set_property IOSTANDARD LVCMOS33 [get_ports {uart_rx}]
set_property PULLUP true [get_ports {uart_rx}]
set_property PACKAGE_PIN U12 [get_ports {uart_tx}]
set_property IOSTANDARD LVCMOS33 [get_ports {uart_tx}]
set_property DRIVE 4 [get_ports {uart_tx}]
set_property SLEW SLOW [get_ports {uart_tx}]

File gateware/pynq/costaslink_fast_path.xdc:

# costaslink_fast_path.xdc: the receive-to-transmit paths' timing (Prompt 36; turnaround.v).  Written by
# hand, not by gen_xdc.py: it names no pin and changes no pin's standard.  Implementation only (build.tcl).
#
# The fast path: the five comparators through their ISERDESE2s' combinational O (fast_sampler_7series.v),
# per ladder bit two reloadable 5-input LUTs (fp_lut5_7series.v: CFGLUT5, which Vivado places as SRLC32E)
# and one LUT with the arm and the registered pin, to the four ladder pins' output buffers (the IOBUFs
# u_lad_* in costaslink_pynq.v): pin to pin, no clock.  The generated costaslink_pynq.xdc makes every path
# from an input port and to an output port false, and a false path outranks set_max_delay (Vivado 2024.1
# has no reset_path), so the constraint goes on the fabric's segment, from the ISERDESE2s' O to the output
# buffers' I: set_max_delay there makes both pins timing endpoints (path segmentation; Vivado says so with
# critical warnings 18-514 and 18-515, expected).  The buffers' own delays are fixed by the I/O standard
# and the pins; fast_path_report.tcl adds them back (port -> D -> O, O -> I, I -> O).
#
# The pins are on two sides of the die: CMP_I, CMP_QP, CMP_QN, CMP_IN and TX_I0, TX_Q0, TX_Q1 on bank 13
# (the left column, X0), CMP_IP on bank 35 and TX_I1 on bank 34 (the right, X1).  A path across is several
# ns of routing that no placement removes.  With one number for all, the placer balances each bit's LUTs
# between its far input and its near ones, mid-die, and every path comes out ~12 ns; so each group has its
# own number, and the same-side paths keep their LUTs by their pads.  (g_in?k? is g_in[k]: brackets do not
# match in a filter.)
#
# The ladder pins' register (tx_engine's tx_i / tx_q, with the synchronous reply in it) and the fast path's
# arm copies get the same: the register's clock-to-pad is the synchronous reply's last step, and it was
# unconstrained (any route at all).  The fast path's tables are static (loaded with it disarmed): a clock.
#
# The numbers are a few tenths of a ns over what this design reached with them set out of reach (the
# fabric's segment at the slow corner: left -> left 4.36 ns, left -> TX_I1 7.86, CMP_IP -> left 8.43,
# CMP_IP -> TX_I1 5.61; a register to its buffer 3.74), so the placer and router keep them and a change
# that loses them fails the build (build.tcl refuses a design with negative slack).
set o_left  [get_pins -of_objects [get_cells -hierarchical -filter {REF_NAME == ISERDESE2 && (NAME =~ *u_fs/g_in?0?.u_iserdes || NAME =~ *u_fs/g_in?1?.u_iserdes || NAME =~ *u_fs/g_in?2?.u_iserdes || NAME =~ *u_fs/g_in?4?.u_iserdes)}] -filter {REF_PIN_NAME == O}]
set o_right [get_pins -of_objects [get_cells -hierarchical -filter {REF_NAME == ISERDESE2 && NAME =~ *u_fs/g_in?3?.u_iserdes}] -filter {REF_PIN_NAME == O}]
set i_left  [get_pins -of_objects [get_cells -hierarchical -filter {REF_NAME =~ OBUF* && (NAME =~ *u_lad_i0/* || NAME =~ *u_lad_q0/* || NAME =~ *u_lad_q1/*)}] -filter {REF_PIN_NAME == I}]
set i_right [get_pins -of_objects [get_cells -hierarchical -filter {REF_NAME =~ OBUF* && NAME =~ *u_lad_i1/*}] -filter {REF_PIN_NAME == I}]
set_max_delay 4.6 -from $o_left  -to $i_left
set_max_delay 8.2 -from $o_left  -to $i_right
set_max_delay 8.8 -from $o_right -to $i_left
set_max_delay 6.0 -from $o_right -to $i_right
set_min_delay 0.0 -from $o_left  -to $i_left
set_min_delay 0.0 -from $o_left  -to $i_right
set_min_delay 0.0 -from $o_right -to $i_left
set_min_delay 0.0 -from $o_right -to $i_right

set lad_tab [get_cells -hierarchical -filter {(REF_NAME == CFGLUT5 || REF_NAME =~ SRL*) && NAME =~ *u_lat/g_fast*}]
set lad_ff  [get_cells -hierarchical -filter {REF_NAME =~ FD* && (NAME =~ *u_tx/tx_i_reg* || NAME =~ *u_tx/tx_q_reg* || NAME =~ *u_lat/fp_arm_c_reg*)}]
set_max_delay -datapath_only 10.0 -from $lad_tab -to $i_left
set_max_delay -datapath_only 10.0 -from $lad_tab -to $i_right
set_max_delay -datapath_only 4.0  -from $lad_ff  -to $i_left
set_max_delay -datapath_only 4.0  -from $lad_ff  -to $i_right
set_min_delay 0.0 -from $lad_ff -to $i_left
set_min_delay 0.0 -from $lad_ff -to $i_right
